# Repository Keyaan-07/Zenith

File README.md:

# Zenith

Zenith is a small single board computer made with the RK3328 which comes with 512 MegaBytes of DDR3 RAM. Zenith is built to run on battery backups along with USB Type-C power inputs. Features of zenith are:  

- Quad core ARM Cortex-A53 CPU
- 512 MB DDR3 RAM
- SD support
- 100M ethernet
- HDMI out
- 24 bit audio
- 1x USB 3.0 2x USB 2.0

I made this SBC because i wanted to locally host some slack bots. There is literally no other reason. I have not compiled buildroot because i'll be using a prebuilt version from ROCK64. A small reason for this is because my laptop probably cannot handle compiling linux. 

Check out this project on [KiCanvas](https://kicanvas.org/?repo=https%3A%2F%2Fgithub.com%2FKeyaan-07%2FZenith%2Ftree%2Fmain%2Fhardware)!  
To check schematics, please go to the above link, imaging every page and putting it here would clutter the README.

## Assembly guide:  
1. clone the repo and head to production: 
```bash
git clone https://Github.com/Keyaan-07/Zenith
cd Zenith/hardware/production
```
2. go to your preferred PCB manufacturer and upload the gerber files there. 
3. get the PCBA option for both(or one) sides.
4. Build the firmware from the [buildroot](https://github.com/buildroot/buildroot) repo.
5. flash it to the SD card using [rufus.ie](https://rufus.ie)
6. plug the SD card in and start the board. 

# BOM

|Designator                                                                                                                                                                                                                                              |Function          |Value           |Quantity|Price |Amount  |Link                                              |
|--------------------------------------------------------------------------------------------------------------------------------------------------------------------------------------------------------------------------------------------------------|------------------|----------------|--------|------|--------|--------------------------------------------------|
|PCB                                                                                                                                                                                                                                                     |PCB               |85x55mm         |5       |9.6   |48      |https://jlcpcb.com/                               |
|PCBA                                                                                                                                                                                                                                                    |Standard          |PCBA            |2       |42.75 |85.5    |https://jlcpcb.com/                               |
|BT1, BT2                                                                                                                                                                                                                                                |Battery Connectors|Battery_Cell    |4       |      |0       |                                                  |
|C0, C1, C10, C11, C12, C13, C14, C15, C16, C17, C18, C19, C2, C21, C22, C23, C24, C25, C26, C27, C28, C29, C3, C30, C31, C32, C33, C35, C37, C4, C40, C42, C47, C48, C5, C51, C52, C53, C54, C55, C58, C6, C62, C64, C67, C7, C70, C71, C74, C75, C8, C9|Capacitor         |100n            |104     |0.001 |0.104   |https://www.lcsc.com/product-detail/C49062.html   |
|C20, C34, C36, C38, C39, C41, C43, C44, C45, C46, C49, C50, C56, C57, C59, C63, C66                                                                                                                                                                     |Capacitor         |10u             |34      |0.03  |1.02    |https://www.lcsc.com/product-detail/C96446.html   |
|C60, C61                                                                                                                                                                                                                                                |Capacitor         |15p             |4       |0.0013|0.0052  |https://www.lcsc.com/product-detail/C277480.html  |
|C65, C68                                                                                                                                                                                                                                                |Capacitor         |1u              |4       |0.009 |0.036   |https://www.lcsc.com/product-detail/C307385.html  |
|C72, C73                                                                                                                                                                                                                                                |Capacitor         |47n             |4       |0.0044|0.0176  |https://www.lcsc.com/product-detail/C2930549.html |
|D1                                                                                                                                                                                                                                                      |LED               |LED             |2       |0.009 |0.018   |https://www.lcsc.com/product-detail/C7496805.html |
|J1                                                                                                                                                                                                                                                      |Ethernet magjack  |-               |2       |1.5   |3       |https://www.lcsc.com/product-detail/C12074.html   |
|J2                                                                                                                                                                                                                                                      |HDMI              |-               |2       |1.5   |3       |https://www.lcsc.com/product-detail/C916313.html  |
|J3                                                                                                                                                                                                                                                      |Micro SD Connector|-               |2       |0.68  |1.36    |https://www.lcsc.com/product-detail/C585350.html  |
|J4                                                                                                                                                                                                                                                      |UART header       |-               |2       |DNP   |DNP     |DNP                                               |
|J5                                                                                                                                                                                                                                                      |Audiojack         |-               |2       |0.05  |0.1     |https://www.lcsc.com/product-detail/C431535.html  |
|J6, J7, J8, J9                                                                                                                                                                                                                                          |USB-C             |-               |8       |0.5   |4       |https://www.lcsc.com/product-detail/C5156605.html |
|L1, L2, L3, L4, L5, L6                                                                                                                                                                                                                                  |Inductors         |2.2u            |12      |0.03  |0.36    |https://www.lcsc.com/product-detail/C45385204.html|
|Q1                                                                                                                                                                                                                                                      |MOSFET            |2N7002          |2       |0.05  |0.1     |https://www.lcsc.com/product-detail/C81445.html   |
|Q2                                                                                                                                                                                                                                                      |MOSFET            |AON7262e        |2       |0.58  |1.16    |https://www.lcsc.com/product-detail/C176755.html  |
|R1                                                                                                                                                                                                                                                      |Resistor          |240             |2       |0.0009|0.0018  |https://www.lcsc.com/product-detail/C270354.html  |
|R11, R17, R2, R26, R27, R3, R30, R31, R32, R33, R35, R38, R40, R5, R6, R8, R9                                                                                                                                                                           |Resistor          |10k             |34      |0.0007|0.0238  |https://www.lcsc.com/product-detail/C7467266.html |
|R12, R41                                                                                                                                                                                                                                                |Resistor          |35k             |4       |0.0015|0.006   |https://www.lcsc.com/product-detail/C180320.html  |
|R13, R14, R15, R18, R19, R20                                                                                                                                                                                                                            |Resistor          |R               |12      |-     |0       |-                                                 |
|R16                                                                                                                                                                                                                                                     |Resistor          |56k             |2       |0.0008|0.0016  |https://www.lcsc.com/product-detail/C18164325.html|
|R21                                                                                                                                                                                                                                                     |Resistor          |10m             |2       |0.14  |0.28    |https://www.lcsc.com/product-detail/C6250315.html |
|R22, R23, R24, R25, R34                                                                                                                                                                                                                                 |Resistor          |100             |10      |0.0009|0.009   |https://www.lcsc.com/product-detail/C270366.html  |
|R28, R29                                                                                                                                                                                                                                                |Resistor          |0R              |4       |0.0009|0.0036  |https://www.lcsc.com/product-detail/C106228.html  |
|R36, R37, R39                                                                                                                                                                                                                                           |Resistor          |5.1k            |6       |0.0007|0.0042  |https://www.lcsc.com/product-detail/C7467269.html |
|R4                                                                                                                                                                                                                                                      |Resistor          |6.6k            |2       |0.0008|0.0016  |https://www.lcsc.com/product-detail/C423452.html  |
|U1                                                                                                                                                                                                                                                      |RAM               |NT5CB256M16ER-FL|2       |13.15 |26.3    |https://www.lcsc.com/product-detail/C2841154.html |
|U10                                                                                                                                                                                                                                                     |SoC               |BQ29209DRBR     |2       |0.76  |1.52    |https://www.lcsc.com/product-detail/C139352.html  |
|U2                                                                                                                                                                                                                                                      |main IC           |RK3328          |2       |8.65  |17.3    |https://www.lcsc.com/product-detail/C2932939.html |
|U3                                                                                                                                                                                                                                                      |ESD IC for HDMI   |TPD12S016PWR    |2       |0.8382|1.6764  |https://www.lcsc.com/product-detail/C201665.html  |
|U4                                                                                                                                                                                                                                                      |Buck              |TPS565201       |2       |0.64  |1.28    |https://www.lcsc.com/product-detail/C327676.html  |
|U5                                                                                                                                                                                                                                                      |Battery charger   |BQ25690RBAR     |2       |6.3   |12.6    |https://www.lcsc.com/product-detail/C53283868.html|
|U6, U7, U8, U9                                                                                                                                                                                                                                          |Buck              |TPS563252DRLR   |8       |1.05  |8.4     |https://www.lcsc.com/product-detail/C19188399.html|
|Y1                                                                                                                                                                                                                                                      |Crystal           |24MHz           |2       |0.58  |1.16    |https://www.lcsc.com/product-detail/C41383245.html|
|                                                                                                                                                                                                                                                        |                  |                |        |      |        |                                                  |
|                                                                                                                                                                                                                                                        |                  |                |        |      |        |                                                  |
|                                                                                                                                                                                                                                                        |                  |                |        |      |        |                                                  |
|                                                                                                                                                                                                                                                        |                  |                |        |      |134.8488|                                                  |

### Onshape link
[here](https://cad.onshape.com/documents/332461f2f869658015d1b4b3/w/bc37113696b38b58a706d278/e/a246ca9cc7cf7bf594e6cd93) is the onshape link for the project

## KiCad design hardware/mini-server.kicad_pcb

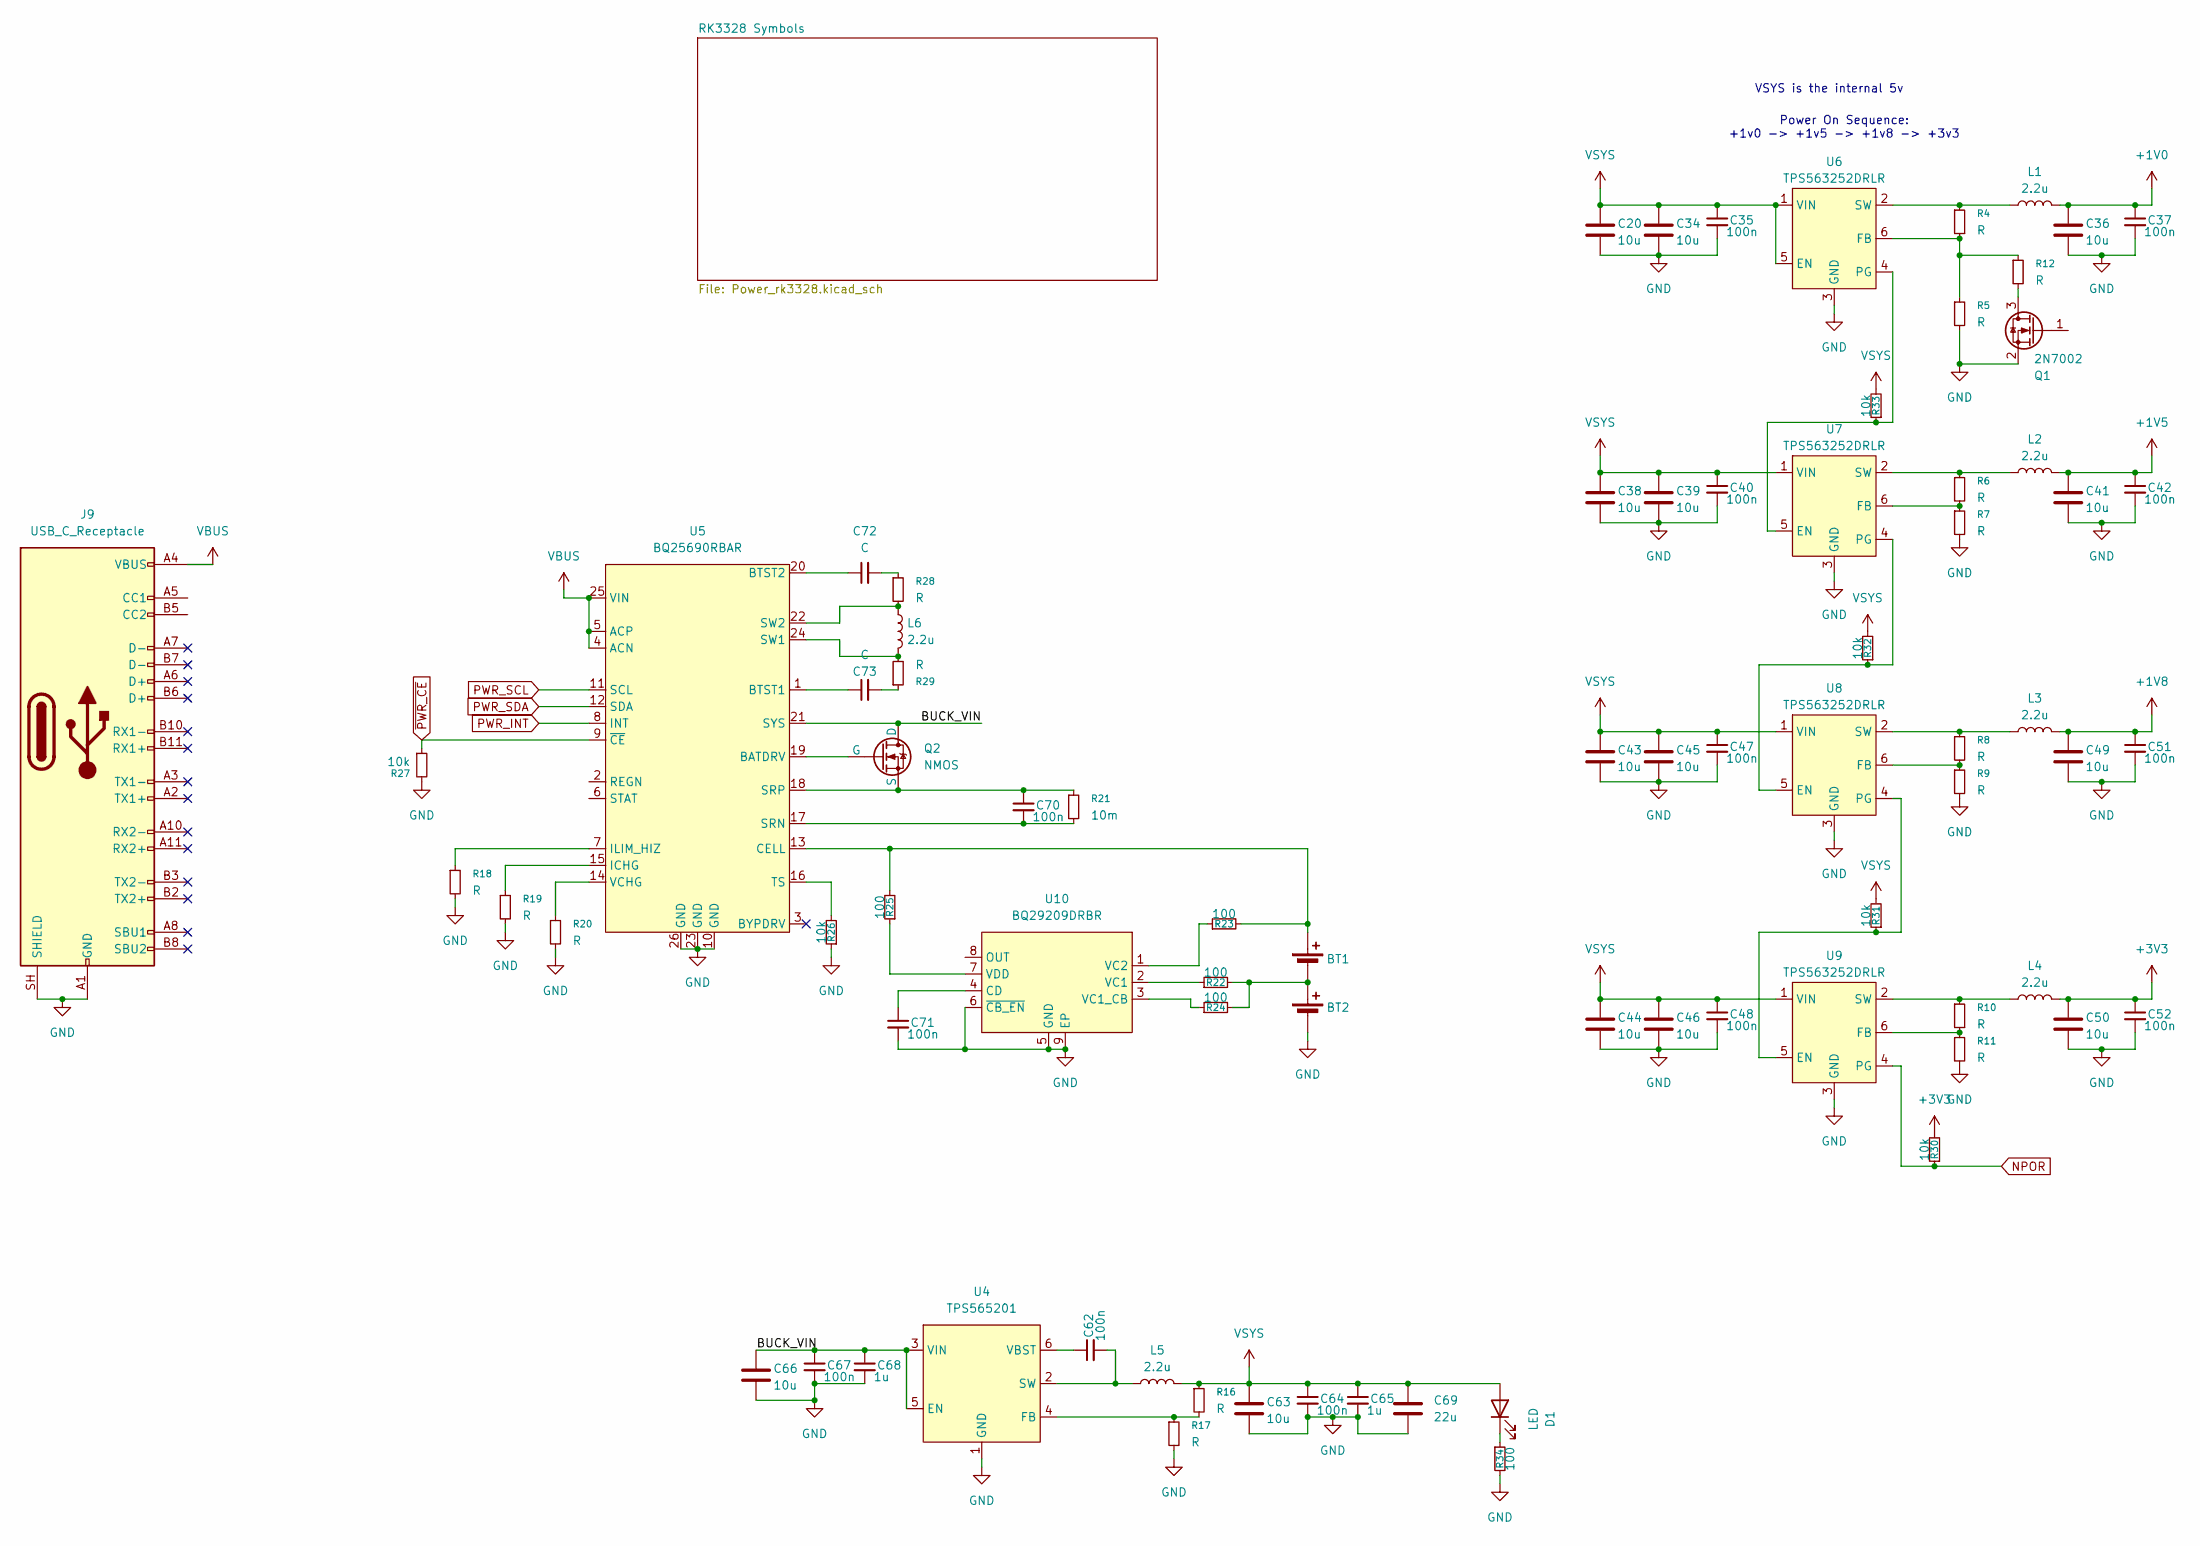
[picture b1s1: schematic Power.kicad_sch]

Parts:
BT1, BT2: Battery_Cell; JST_XH_B2B-XH-AM_1x02_P2.50mm_Vertical
C20, C34, C36, C38, C39, C41, C43, C44, C45, C46, C49, C50, C63, C66: 10u; C_0603_1608Metric
C35, C37, C40, C42, C47, C48, C51, C52, C62, C64, C67, C70, C71: 100n; C_0201_0603Metric
C65, C68: 1u; C_0201_0603Metric
C69: 22u; C_0603_1608Metric
C72, C73: C; C_0201_0603Metric
D1: LED; LED_0402_1005Metric
J9: USB_C_Receptacle; USB_C_Receptacle_Molex_105450-0101
L1, L2, L3, L4, L5, L6: 2.2u; L_1008_2520Metric
Q1: 2N7002; SOT-23
Q2: NMOS
R4, R5, R6, R7, R8, R9, R10, R11, R12, R16, R17, R18, R19, R20, R28, R29: R; R_0201_0603Metric
R21: 10m; R_0402_1005Metric
R22, R23, R24, R25, R34: 100; R_0201_0603Metric
R26, R27, R30, R31, R32, R33: 10k; R_0201_0603Metric
U4: TPS565201; SOT-23-6
U5: BQ25690RBAR; WQFN-26_L4.0-W3.5_BQ25690RBAR; MPN BQ25690RBAR; LCSC Part C53283868
U6, U7, U8, U9: TPS563252DRLR; SOT-563-6_L1.6-W1.2-P0.50-LS1.6-BL; MPN TPS563252DRLR; LCSC Part C19188399
U10: BQ29209DRBR; VSON-8-1EP_3x3mm_P0.65mm_EP1.6x2.4mm; MPN BQ29209DRBR; LCSC Part C139352

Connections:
+1V0: C36.1, C37.1, L1.2; also elsewhere on the board
+1V5: C41.1, C42.1, L2.2; also elsewhere on the board
+1V8: C49.1, C51.1, L3.2; also elsewhere on the board
+3V3: C50.1, C52.1, L4.2, R30.2; also elsewhere on the board
/Power/BUCK_VIN: C66.1, C67.1, C68.1, Q2.1 (D), U4.3 (VIN), U4.5 (EN), U5.21 (SYS)
GND: BT2.2 (-), C20.2, C34.2, C35.2, C36.2, C37.2, C38.2, C39.2, C40.2, C41.2, C42.2, C43.2, C44.2, C45.2, C46.2, C47.2, C48.2, C49.2, C50.2, C51.2, C52.2, C63.2, C64.2, C65.2, C66.2, C67.2, C68.2, C69.2, C71.2, J9.A1 (GND), J9.A12 (GND), J9.B1 (GND), J9.B12 (GND), J9.SH (SHIELD), Q1.2 (S), R5.2, R7.2, R9.2, R11.2, R17.2, R18.2, R19.2, R20.2, R26.1, R27.2, R34.2, U4.1 (GND), U5.10 (GND), U5.23 (GND), U5.26 (GND), U6.3 (GND), U7.3 (GND), U8.3 (GND), U9.3 (GND), U10.5 (GND), U10.6 (~CB_EN), U10.9 (EP); also elsewhere on the board
NPOR: R30.1, U9.4 (PG); also elsewhere on the board
unnamed: BT1.1 (+), R23.2, R25.2, U5.13 (CELL)
unnamed: BT1.2 (-), BT2.1 (+), R22.2, R24.2
unnamed: C72.2, R28.1
unnamed: C73.2, R29.1
unnamed: D1.1 (K), R34.1
unnamed: Q1.3 (D), R12.2
unnamed: Q2.2 (G), U5.19 (BATDRV)
unnamed: C70.1, Q2.3 (S), R21.1, U5.18 (SRP)
unnamed: R16.2, R17.1, U4.4 (FB)
unnamed: C62.2, L5.1, U4.2 (SW)
unnamed: C62.1, U4.6 (VBST)
unnamed: C73.1, U5.1 (BTST1)
unnamed: C72.1, U5.20 (BTST2)
unnamed: R19.1, U5.15 (ICHG)
unnamed: R18.1, U5.7 (ILIM_HIZ)
unnamed: C70.2, R21.2, U5.17 (SRN)
unnamed: L6.2, R29.2, U5.24 (SW1)
unnamed: L6.1, R28.2, U5.22 (SW2)
unnamed: R26.2, U5.16 (TS)
unnamed: R20.1, U5.14 (VCHG)
unnamed: R4.2, R5.1, R12.1, U6.6 (FB)
unnamed: R33.1, U6.4 (PG), U7.5 (EN)
unnamed: L1.1, R4.1, U6.2 (SW)
unnamed: R6.2, R7.1, U7.6 (FB)
unnamed: R32.1, U7.4 (PG), U8.5 (EN)
unnamed: L2.1, R6.1, U7.2 (SW)
unnamed: R8.2, R9.1, U8.6 (FB)
unnamed: R31.1, U8.4 (PG), U9.5 (EN)
unnamed: L3.1, R8.1, U8.2 (SW)
unnamed: R10.2, R11.1, U9.6 (FB)
unnamed: L4.1, R10.1, U9.2 (SW)
unnamed: C71.1, U10.4 (CD)
unnamed: R22.1, U10.2 (VC1)
unnamed: R24.1, U10.3 (VC1_CB)
unnamed: R23.1, U10.1 (VC2)
unnamed: R25.1, U10.7 (VDD)
PWR_INT: U5.8 (INT); also elsewhere on the board
PWR_SCL: U5.11 (SCL); also elsewhere on the board
PWR_SDA: U5.12 (SDA); also elsewhere on the board
VBUS: J9.A4 (VBUS), J9.A9 (VBUS), J9.B4 (VBUS), J9.B9 (VBUS), U5.4 (ACN), U5.5 (ACP), U5.25 (VIN)
VSYS: C20.1, C34.1, C35.1, C38.1, C39.1, C40.1, C43.1, C44.1, C45.1, C46.1, C47.1, C48.1, C63.1, C64.1, C65.1, C69.1, D1.2 (A), L5.2, R16.1, R31.2, R32.2, R33.2, U6.1 (VIN), U6.5 (EN), U7.1 (VIN), U8.1 (VIN), U9.1 (VIN); also elsewhere on the board
~PWR_CE: R27.1, U5.9 (~CE); also elsewhere on the board

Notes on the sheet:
Power On Sequence: +1v0 -> +1v5 -> +1v8 -> +3v3
VSYS is the internal 5v

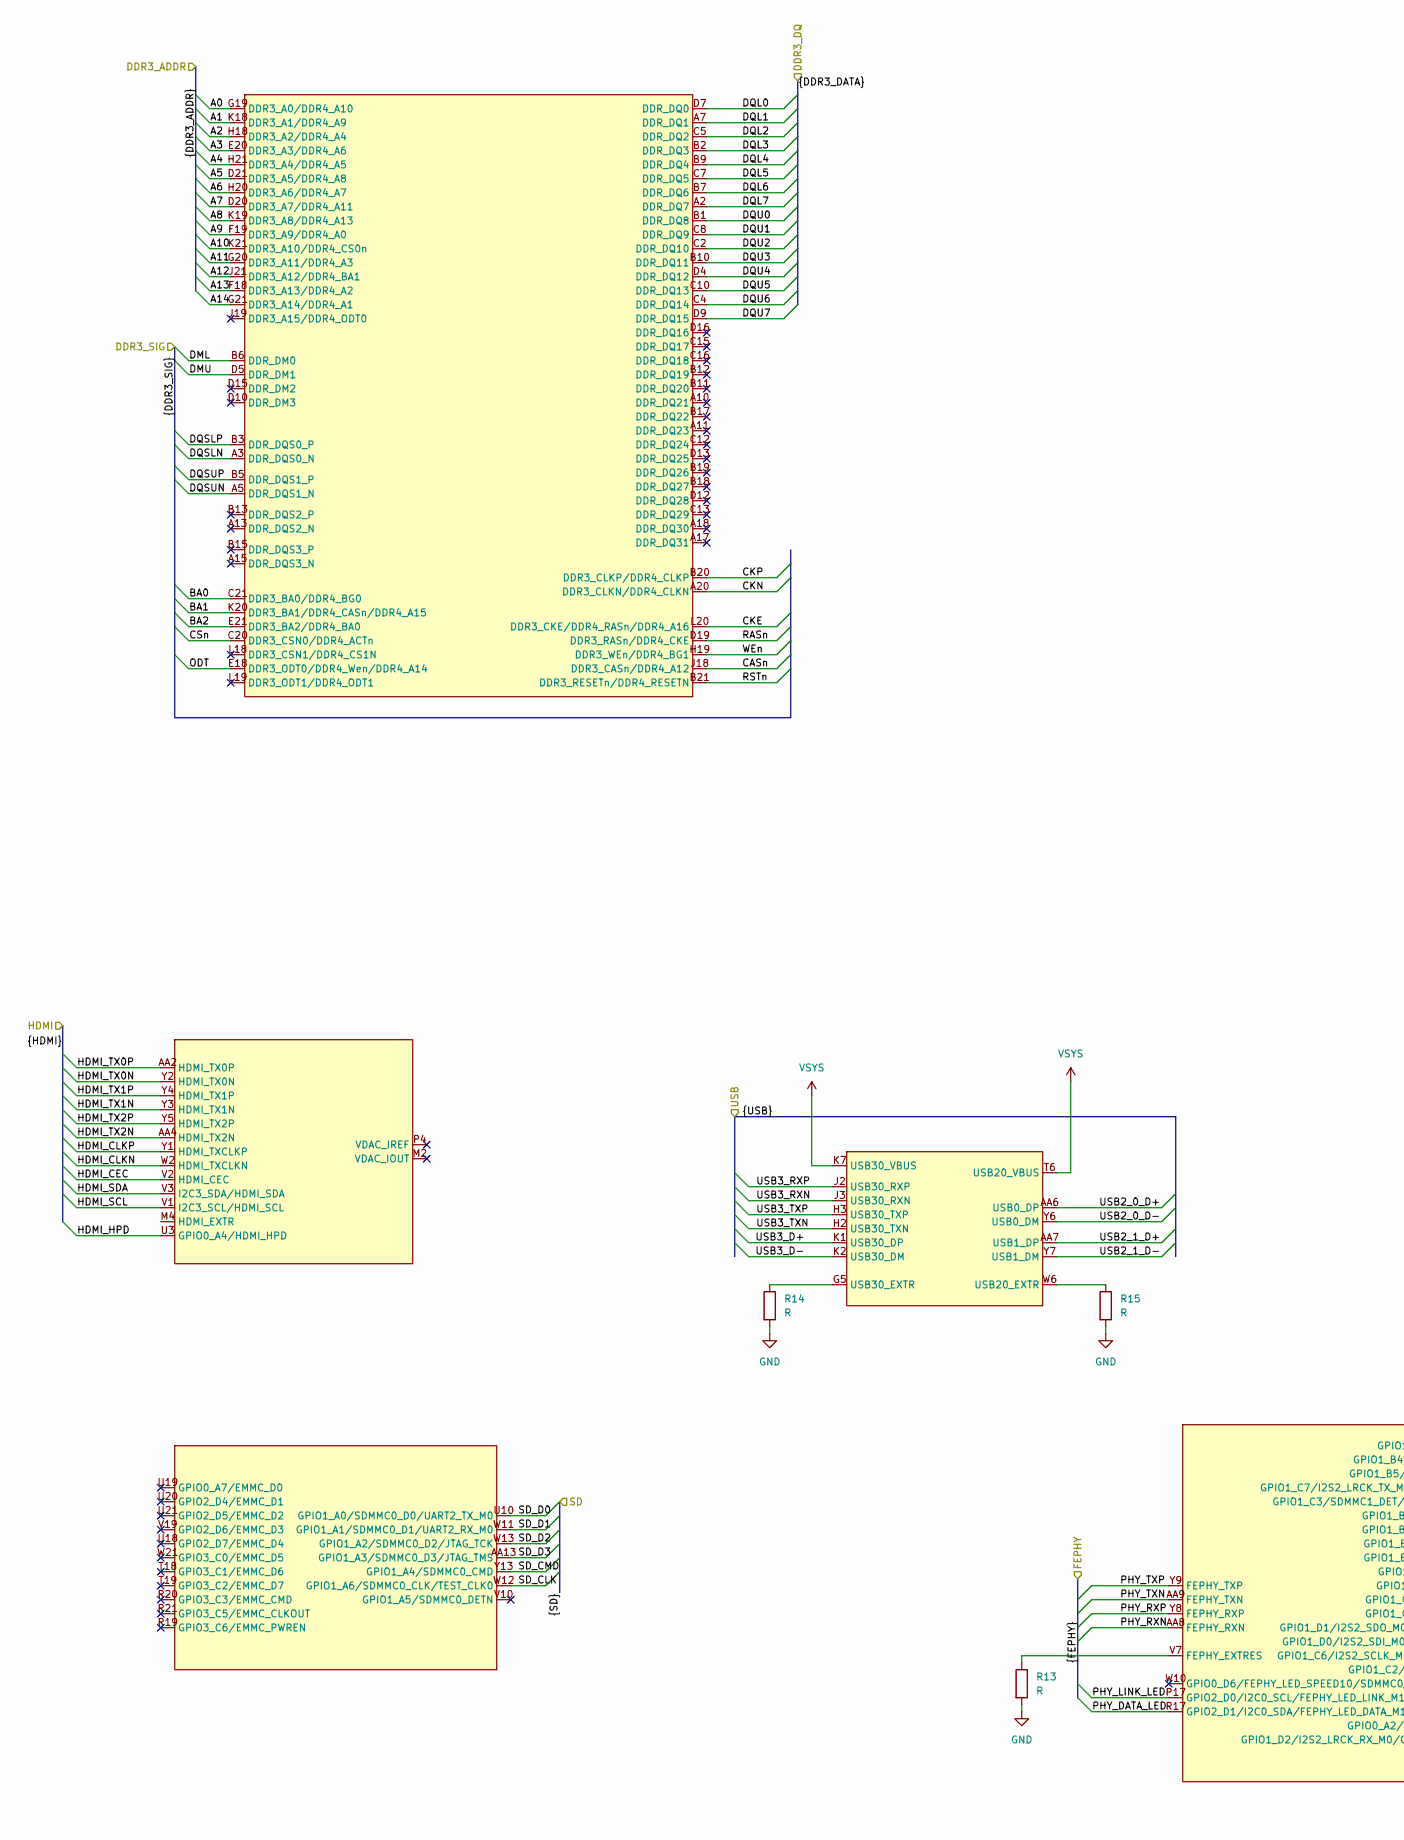
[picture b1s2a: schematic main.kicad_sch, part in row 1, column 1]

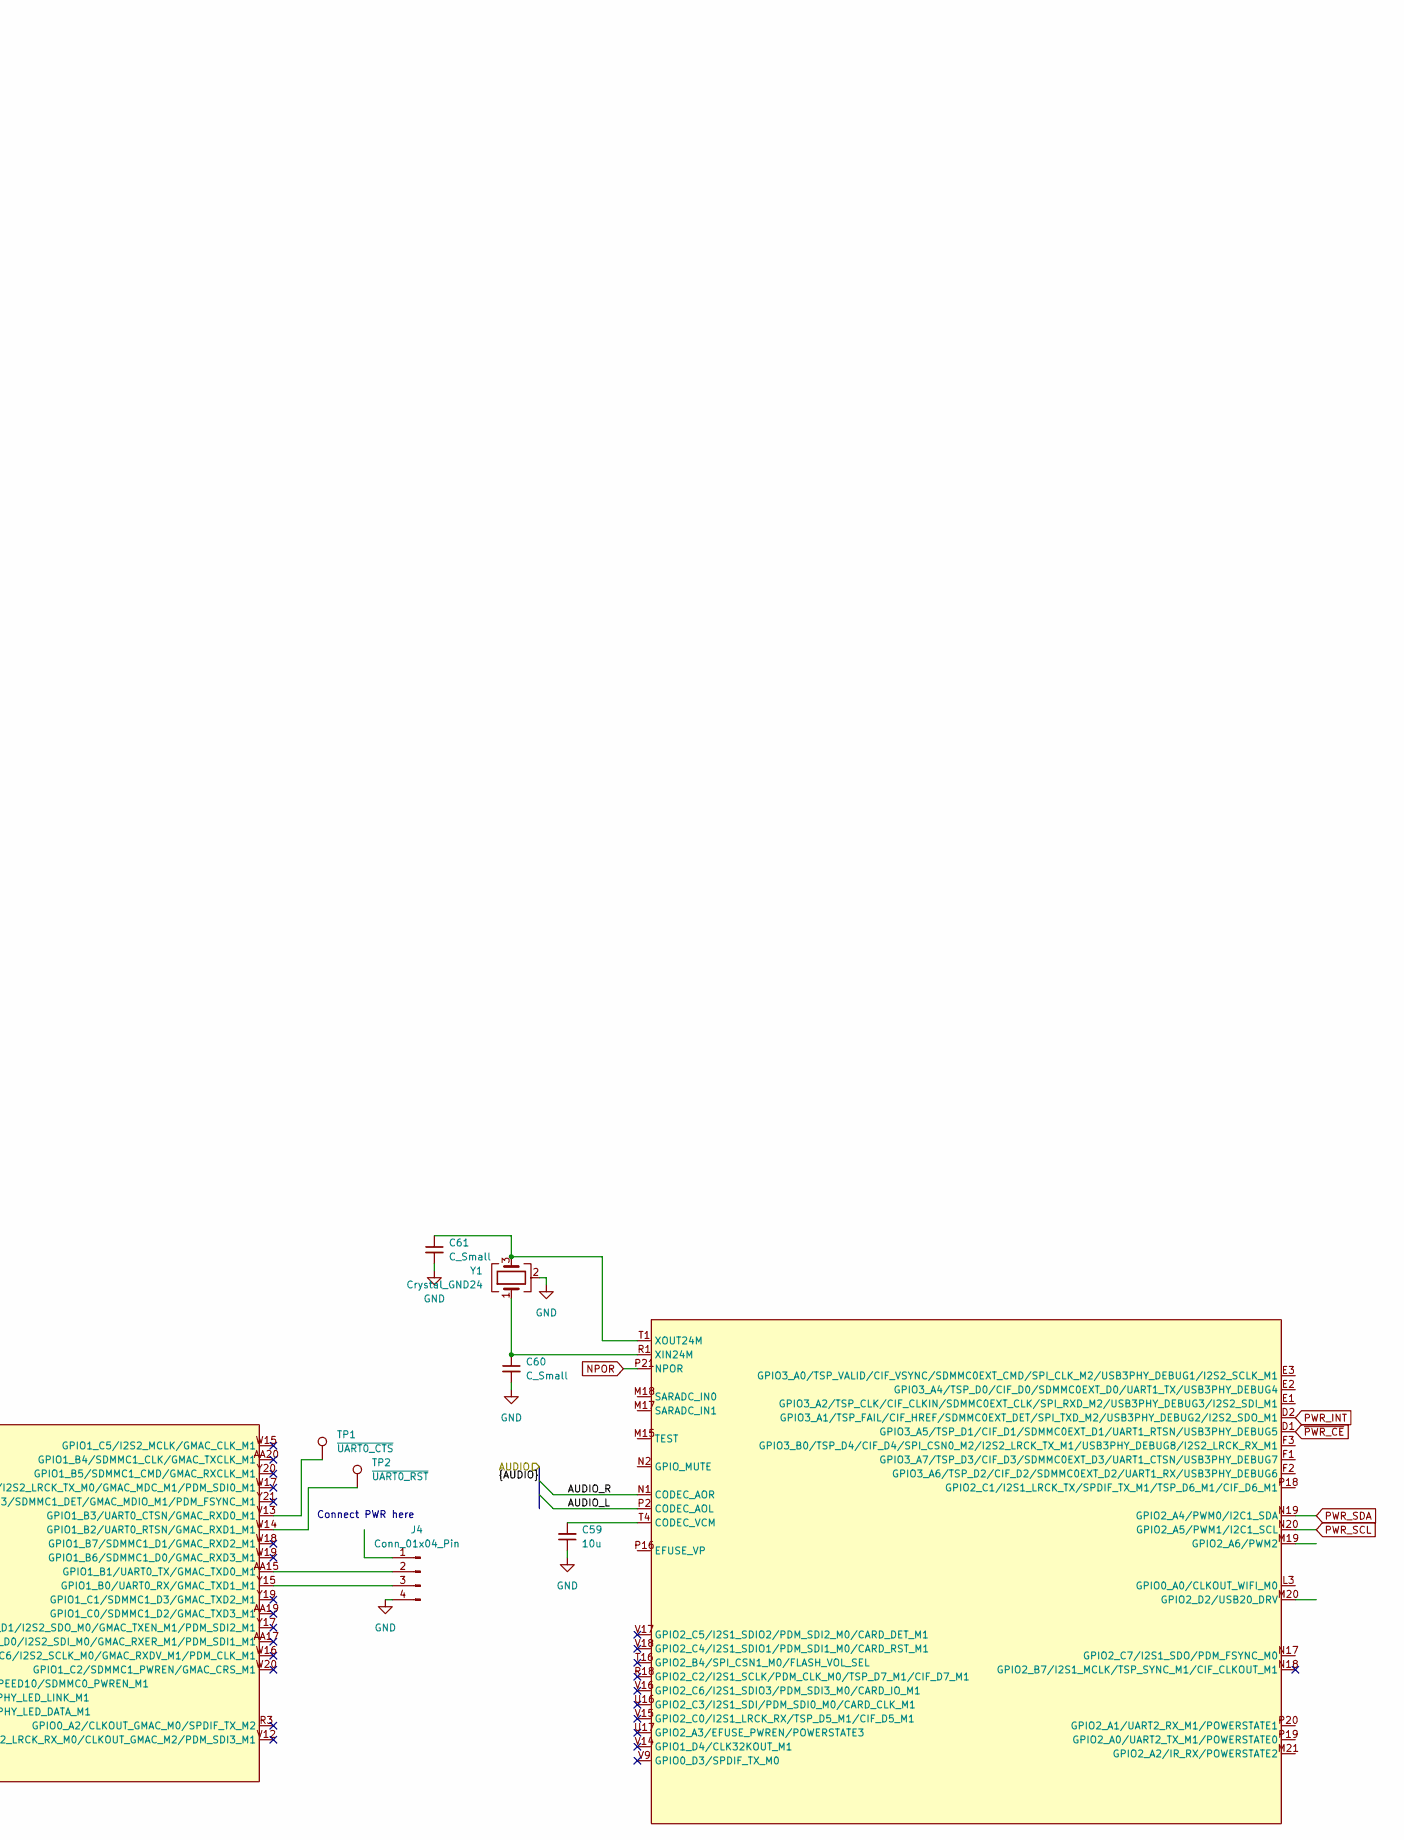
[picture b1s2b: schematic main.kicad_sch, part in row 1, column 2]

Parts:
C59: 10u; C_0603_1608Metric
C60, C61: C_Small; C_0201_0603Metric
J4: Conn_01x04_Pin; PinHeader_1x04_P2.54mm_Vertical
R13, R14, R15: R; R_0201_0603Metric
TP1: ~{UART0_CTS}; TestPoint_Pad_D1.0mm
TP2: ~{UART0_RST}; TestPoint_Pad_D1.0mm
U2: RK3328; TFBGA395_L14.0-W14.0_RK3328; MPN RK3328; LCSC Part C2932939
Y1: Crystal_GND24; Crystal_SMD_3225-4Pin_3.2x2.5mm

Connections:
/Audio/AUDIO_L: U2.P2 (CODEC_AOL); also elsewhere on the board
/Audio/AUDIO_R: U2.N1 (CODEC_AOR); also elsewhere on the board
/DDR3/A0: U2.G19 (DDR3_A0/DDR4_A10); also elsewhere on the board
/DDR3/A1: U2.K18 (DDR3_A1/DDR4_A9); also elsewhere on the board
/DDR3/A2: U2.H18 (DDR3_A2/DDR4_A4); also elsewhere on the board
/DDR3/A3: U2.E20 (DDR3_A3/DDR4_A6); also elsewhere on the board
/DDR3/A4: U2.H21 (DDR3_A4/DDR4_A5); also elsewhere on the board
/DDR3/A5: U2.D21 (DDR3_A5/DDR4_A8); also elsewhere on the board
/DDR3/A6: U2.H20 (DDR3_A6/DDR4_A7); also elsewhere on the board
/DDR3/A7: U2.D20 (DDR3_A7/DDR4_A11); also elsewhere on the board
/DDR3/A8: U2.K19 (DDR3_A8/DDR4_A13); also elsewhere on the board
/DDR3/A9: U2.F19 (DDR3_A9/DDR4_A0); also elsewhere on the board
/DDR3/A10: U2.K21 (DDR3_A10/DDR4_CS0n); also elsewhere on the board
/DDR3/A11: U2.G20 (DDR3_A11/DDR4_A3); also elsewhere on the board
/DDR3/A12: U2.J21 (DDR3_A12/DDR4_BA1); also elsewhere on the board
/DDR3/A13: U2.F18 (DDR3_A13/DDR4_A2); also elsewhere on the board
/DDR3/A14: U2.G21 (DDR3_A14/DDR4_A1); also elsewhere on the board
/DDR3/BA0: U2.C21 (DDR3_BA0/DDR4_BG0); also elsewhere on the board
/DDR3/BA1: U2.K20 (DDR3_BA1/DDR4_CASn/DDR4_A15); also elsewhere on the board
/DDR3/BA2: U2.E21 (DDR3_BA2/DDR4_BA0); also elsewhere on the board
/DDR3/CASn: U2.J18 (DDR3_CASn/DDR4_A12); also elsewhere on the board
/DDR3/CKE: U2.L20 (DDR3_CKE/DDR4_RASn/DDR4_A16); also elsewhere on the board
/DDR3/CKN: U2.A20 (DDR3_CLKN/DDR4_CLKN); also elsewhere on the board
/DDR3/CKP: U2.B20 (DDR3_CLKP/DDR4_CLKP); also elsewhere on the board
/DDR3/CSn: U2.C20 (DDR3_CSN0/DDR4_ACTn); also elsewhere on the board
/DDR3/DML: U2.B6 (DDR_DM0); also elsewhere on the board
/DDR3/DMU: U2.D5 (DDR_DM1); also elsewhere on the board
/DDR3/DQL0: U2.D7 (DDR_DQ0); also elsewhere on the board
/DDR3/DQL1: U2.A7 (DDR_DQ1); also elsewhere on the board
/DDR3/DQL2: U2.C5 (DDR_DQ2); also elsewhere on the board
/DDR3/DQL3: U2.B2 (DDR_DQ3); also elsewhere on the board
/DDR3/DQL4: U2.B9 (DDR_DQ4); also elsewhere on the board
/DDR3/DQL5: U2.C7 (DDR_DQ5); also elsewhere on the board
/DDR3/DQL6: U2.B7 (DDR_DQ6); also elsewhere on the board
/DDR3/DQL7: U2.A2 (DDR_DQ7); also elsewhere on the board
/DDR3/DQSLN: U2.A3 (DDR_DQS0_N); also elsewhere on the board
/DDR3/DQSLP: U2.B3 (DDR_DQS0_P); also elsewhere on the board
/DDR3/DQSUN: U2.A5 (DDR_DQS1_N); also elsewhere on the board
/DDR3/DQSUP: U2.B5 (DDR_DQS1_P); also elsewhere on the board
/DDR3/DQU0: U2.B1 (DDR_DQ8); also elsewhere on the board
/DDR3/DQU1: U2.C8 (DDR_DQ9); also elsewhere on the board
/DDR3/DQU2: U2.C2 (DDR_DQ10); also elsewhere on the board
/DDR3/DQU3: U2.B10 (DDR_DQ11); also elsewhere on the board
/DDR3/DQU4: U2.D4 (DDR_DQ12); also elsewhere on the board
/DDR3/DQU5: U2.C10 (DDR_DQ13); also elsewhere on the board
/DDR3/DQU6: U2.C4 (DDR_DQ14); also elsewhere on the board
/DDR3/DQU7: U2.D9 (DDR_DQ15); also elsewhere on the board
/DDR3/ODT: U2.E18 (DDR3_ODT0/DDR4_Wen/DDR4_A14); also elsewhere on the board
/DDR3/RASn: U2.D19 (DDR3_RASn/DDR4_CKE); also elsewhere on the board
/DDR3/RSTn: U2.B21 (DDR3_RESETn/DDR4_RESETN); also elsewhere on the board
/DDR3/WEn: U2.H19 (DDR3_WEn/DDR4_BG1); also elsewhere on the board
/Ethernet/PHY_DATA_LED: U2.R17 (GPIO2_D1/I2C0_SDA/FEPHY_LED_DATA_M1); also elsewhere on the board
/Ethernet/PHY_LINK_LED: U2.P17 (GPIO2_D0/I2C0_SCL/FEPHY_LED_LINK_M1); also elsewhere on the board
/Ethernet/PHY_RXN: U2.AA8 (FEPHY_RXN); also elsewhere on the board
/Ethernet/PHY_RXP: U2.Y8 (FEPHY_RXP); also elsewhere on the board
/Ethernet/PHY_TXN: U2.AA9 (FEPHY_TXN); also elsewhere on the board
/Ethernet/PHY_TXP: U2.Y9 (FEPHY_TXP); also elsewhere on the board
/HDMI/HDMI_CEC: U2.V2 (HDMI_CEC); also elsewhere on the board
/HDMI/HDMI_CLKN: U2.W2 (HDMI_TXCLKN); also elsewhere on the board
/HDMI/HDMI_CLKP: U2.Y1 (HDMI_TXCLKP); also elsewhere on the board
/HDMI/HDMI_HPD: U2.U3 (GPIO0_A4/HDMI_HPD); also elsewhere on the board
/HDMI/HDMI_SCL: U2.V1 (I2C3_SCL/HDMI_SCL); also elsewhere on the board
/HDMI/HDMI_SDA: U2.V3 (I2C3_SDA/HDMI_SDA); also elsewhere on the board
/HDMI/HDMI_TX0N: U2.Y2 (HDMI_TX0N); also elsewhere on the board
/HDMI/HDMI_TX0P: U2.AA2 (HDMI_TX0P); also elsewhere on the board
/HDMI/HDMI_TX1N: U2.Y3 (HDMI_TX1N); also elsewhere on the board
/HDMI/HDMI_TX1P: U2.Y4 (HDMI_TX1P); also elsewhere on the board
/HDMI/HDMI_TX2N: U2.AA4 (HDMI_TX2N); also elsewhere on the board
/HDMI/HDMI_TX2P: U2.Y5 (HDMI_TX2P); also elsewhere on the board
/Storage/SD_CLK: U2.W12 (GPIO1_A6/SDMMC0_CLK/TEST_CLK0); also elsewhere on the board
/Storage/SD_CMD: U2.Y13 (GPIO1_A4/SDMMC0_CMD); also elsewhere on the board
/Storage/SD_D0: U2.U10 (GPIO1_A0/SDMMC0_D0/UART2_TX_M0); also elsewhere on the board
/Storage/SD_D1: U2.W11 (GPIO1_A1/SDMMC0_D1/UART2_RX_M0); also elsewhere on the board
/Storage/SD_D2: U2.W13 (GPIO1_A2/SDMMC0_D2/JTAG_TCK); also elsewhere on the board
/Storage/SD_D3: U2.AA13 (GPIO1_A3/SDMMC0_D3/JTAG_TMS); also elsewhere on the board
/USB/USB2_0_D+: U2.AA6 (USB0_DP); also elsewhere on the board
/USB/USB2_0_D-: U2.Y6 (USB0_DM); also elsewhere on the board
/USB/USB2_1_D+: U2.AA7 (USB1_DP); also elsewhere on the board
/USB/USB2_1_D-: U2.Y7 (USB1_DM); also elsewhere on the board
/USB/USB3_D+: U2.K1 (USB30_DP); also elsewhere on the board
/USB/USB3_D-: U2.K2 (USB30_DM); also elsewhere on the board
/USB/USB3_RXN: U2.J3 (USB30_RXN); also elsewhere on the board
/USB/USB3_RXP: U2.J2 (USB30_RXP); also elsewhere on the board
/USB/USB3_TXN: U2.H2 (USB30_TXN); also elsewhere on the board
/USB/USB3_TXP: U2.H3 (USB30_TXP); also elsewhere on the board
GND: C59.1, C60.2, C61.2, J4.4, R13.2, R14.2, R15.2, Y1.2 (G), Y1.4 (G); also elsewhere on the board
NPOR: U2.P21 (NPOR); also elsewhere on the board
unnamed: J4.2, U2.AA15 (GPIO1_B1/UART0_TX/GMAC_TXD0_M1)
unnamed: J4.3, U2.Y15 (GPIO1_B0/UART0_RX/GMAC_TXD1_M1)
unnamed: R13.1, U2.V7 (FEPHY_EXTRES)
unnamed: TP2.1 (1_1), U2.W14 (GPIO1_B2/UART0_RTSN/GMAC_RXD1_M1)
unnamed: TP1.1 (1_1), U2.V13 (GPIO1_B3/UART0_CTSN/GMAC_RXD0_M1)
unnamed: R15.1, U2.W6 (USB20_EXTR)
unnamed: R14.1, U2.G5 (USB30_EXTR)
unnamed: C59.2, U2.T4 (CODEC_VCM)
unnamed: C60.1, U2.R1 (XIN24M), Y1.1
unnamed: C61.1, U2.T1 (XOUT24M), Y1.3
PWR_INT: U2.D2 (GPIO3_A1/TSP_FAIL/CIF_HREF/SDMMC0EXT_DE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); also elsewhere on the board
PWR_SCL: U2.N20 (GPIO2_A5/PWM1/I2C1_SCL); also elsewhere on the board
PWR_SDA: U2.N19 (GPIO2_A4/PWM0/I2C1_SDA); also elsewhere on the board
VSYS: U2.K7 (USB30_VBUS), U2.T6 (USB20_VBUS); also elsewhere on the board
~PWR_CE: U2.D1 (GPIO3_A5/TSP_D1/CIF_D1/SDMMC0EXT_D1/UAR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); also elsewhere on the board

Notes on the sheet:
Connect PWR here

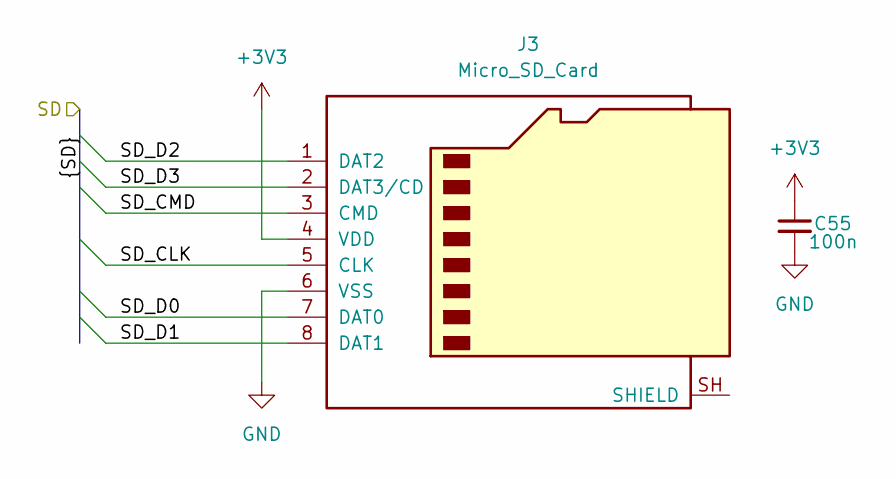
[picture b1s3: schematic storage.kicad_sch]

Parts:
C55: 100n; C_0201_0603Metric
J3: Micro_SD_Card; microSD_HC_Molex_104031-0811

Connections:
+3V3: C55.1, J3.4 (VDD); also elsewhere on the board
/Storage/SD_CLK: J3.5 (CLK); also elsewhere on the board
/Storage/SD_CMD: J3.3 (CMD); also elsewhere on the board
/Storage/SD_D0: J3.7 (DAT0); also elsewhere on the board
/Storage/SD_D1: J3.8 (DAT1); also elsewhere on the board
/Storage/SD_D2: J3.1 (DAT2); also elsewhere on the board
/Storage/SD_D3: J3.2 (DAT3/CD); also elsewhere on the board
GND: C55.2, J3.6 (VSS); also elsewhere on the board
